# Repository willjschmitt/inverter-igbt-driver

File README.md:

# inverter-igbt-driver
IGBT driver for Electric Vehicle Inverter

This project is a work in progress to design a simple IGBT driver for use with the controls designed in https://github.com/willjschmitt/electric-vehicle-controller.

Board is designed in [KiCad](http://kicad-pcb.org/).

## Getting Started
```
git clone https://github.com/willjschmitt/inverter-igbt-driver
```

Install KiCad. Open up the KiCad project!

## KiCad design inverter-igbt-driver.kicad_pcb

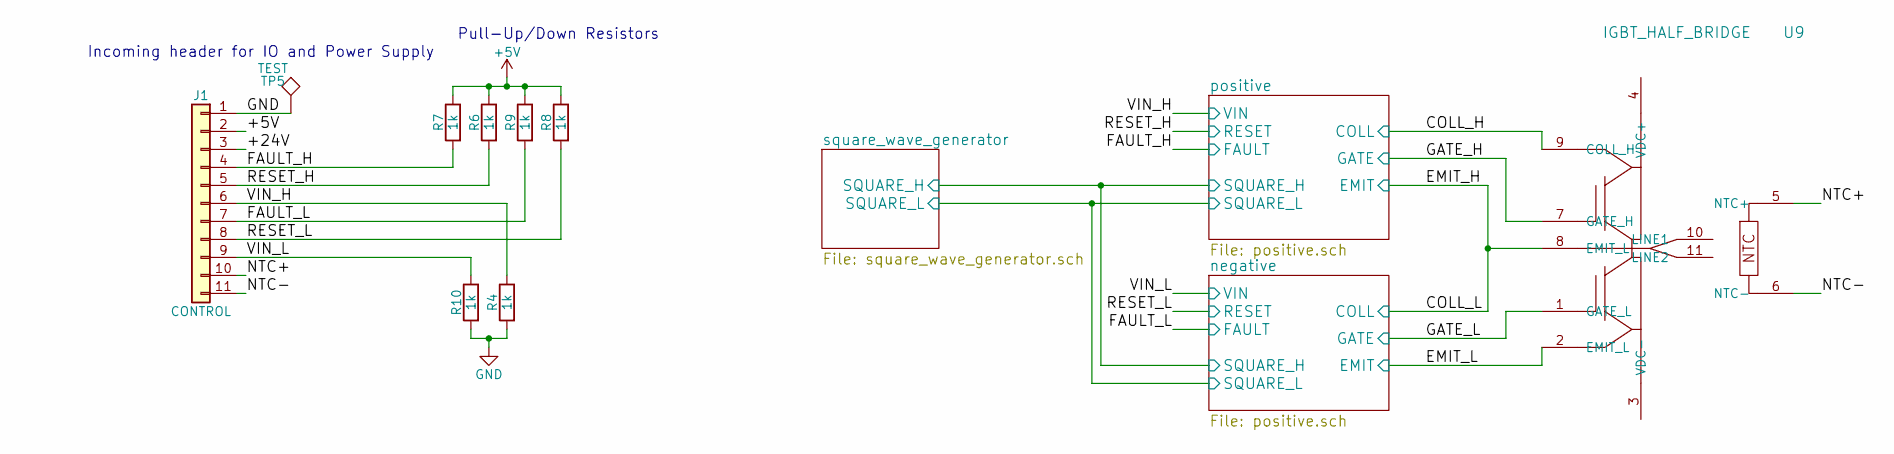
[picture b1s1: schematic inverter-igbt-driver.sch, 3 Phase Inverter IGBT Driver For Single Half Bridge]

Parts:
J1: CONTROL; Pin_Header_Straight_1x11_Pitch2.54mm
R4, R6, R7, R8, R9, R10: 1k; R_0402
TP5: TEST; TP RCT (0805)
U9: IGBT_HALF_BRIDGE; MG06600WB-BN4MM

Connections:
+5V: J1.2, R6.1, R7.1, R8.1, R9.1; also elsewhere on the board
+24V: J1.3; also elsewhere on the board
/COLL_H: U9.9 (COLL_H); also elsewhere on the board
/COLL_L: U9.8 (EMIT_L); also elsewhere on the board
/EMIT_L: U9.2 (EMIT_L); also elsewhere on the board
/FAULT_H: J1.4, R7.2; also elsewhere on the board
/FAULT_L: J1.7, R9.2; also elsewhere on the board
/GATE_H: U9.7 (GATE_H); also elsewhere on the board
/GATE_L: U9.1 (GATE_L); also elsewhere on the board
/NTC+: J1.10, U9.5 (NTC+)
/NTC-: J1.11, U9.6 (NTC-)
/RESET_H: J1.5, R6.2; also elsewhere on the board
/RESET_L: J1.8, R8.2; also elsewhere on the board
/VIN_H: J1.6, R4.1; also elsewhere on the board
/VIN_L: J1.9, R10.1; also elsewhere on the board
GND: J1.1, R4.2, R10.2, TP5.1; also elsewhere on the board

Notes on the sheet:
Incoming header for IO and Power Supply
Pull-Up/Down Resistors

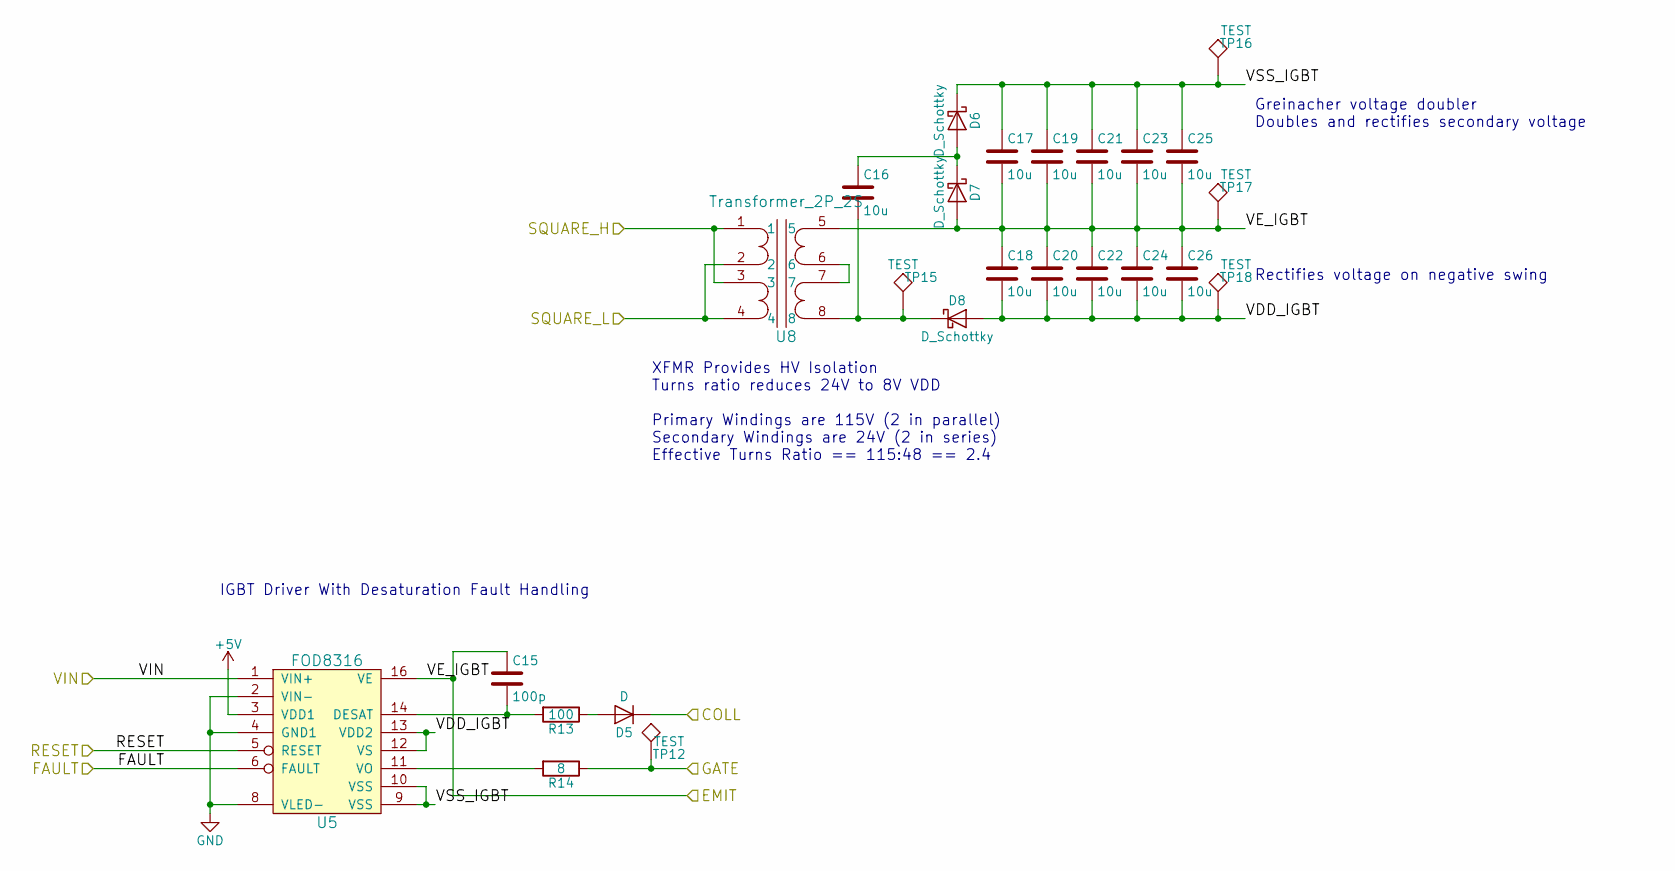
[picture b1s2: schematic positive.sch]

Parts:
C2, C3, C4, C5, C6, C7, C8, C9, C10, C11, C12: 10u; C_1206_HandSoldering
C13: 100p; C_1206_HandSoldering
D1, D2, D3: D_Schottky; D_SOD-123F
D4: D; DO-214AC
R2: 100; R_1206_HandSoldering
R3: 8; R_Axial_DIN0207_L6.3mm_D2.5mm_P7.62mm_Horizontal
TP4, TP6, TP7, TP8, TP9: TEST; TP RCT (0805)
U3: FOD8316; SOIC-16W_7.5x10.3mm_Pitch1.27mm
U6: Transformer_2P_2S; FS48-050-C2

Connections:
+5V: U3.3 (VDD1); also elsewhere on the board
/COLL_H: D4.1 (K); also elsewhere on the board
/COLL_L: C3.2, C4.1, C5.2, C6.1, C7.2, C8.1, C9.2, C10.1, C11.2, C12.1, C13.1, D2.2 (A), TP8.1, U3.16 (VE), U6.5; also elsewhere on the board
/FAULT_H: U3.6 (FAULT); also elsewhere on the board
/GATE_H: R3.1, TP4.1; also elsewhere on the board
/RESET_H: U3.5 (RESET); also elsewhere on the board
/VIN_H: U3.1 (VIN+); also elsewhere on the board
/negative/SQUARE_H: U6.1, U6.3; also elsewhere on the board
/negative/SQUARE_L: U6.2, U6.4; also elsewhere on the board
/positive/VDD_IGBT: C4.2, C6.2, C8.2, C10.2, C12.2, D3.2 (A), TP9.1, U3.12 (VS), U3.13 (VDD2)
/positive/VSS_IGBT: C3.1, C5.1, C7.1, C9.1, C11.1, D1.1 (K), TP7.1, U3.9 (VSS), U3.10 (VSS)
GND: U3.2 (VIN-), U3.4 (GND1), U3.8 (VLED-); also elsewhere on the board
unnamed: C2.1, D1.2 (A), D2.1 (K)
unnamed: C2.2, D3.1 (K), TP6.1, U6.8
unnamed: C13.2, R2.2, U3.14 (DESAT)
unnamed: D4.2 (A), R2.1
unnamed: R3.2, U3.11 (VO)
unnamed: U6.6, U6.7

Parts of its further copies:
C15: 100p; C_1206_HandSoldering
C16, C17, C18, C19, C20, C21, C22, C23, C24, C25, C26: 10u; C_1206_HandSoldering
D5: D; DO-214AC
D6, D7, D8: D_Schottky; D_SOD-123F
R13: 100; R_1206_HandSoldering
R14: 8; R_Axial_DIN0207_L6.3mm_D2.5mm_P7.62mm_Horizontal
TP12, TP15, TP16, TP17, TP18: TEST; TP RCT (0805)
U5: FOD8316; SOIC-16W_7.5x10.3mm_Pitch1.27mm
U8: Transformer_2P_2S; FS48-050-C2

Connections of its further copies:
+5V: U5.3 (VDD1); also elsewhere on the board
/COLL_L: D5.1 (K); also elsewhere on the board
/EMIT_L: C15.1, C17.2, C18.1, C19.2, C20.1, C21.2, C22.1, C23.2, C24.1, C25.2, C26.1, D7.2 (A), TP17.1, U5.16 (VE), U8.5; also elsewhere on the board
/FAULT_L: U5.6 (FAULT); also elsewhere on the board
/GATE_L: R14.1, TP12.1; also elsewhere on the board
/RESET_L: U5.5 (RESET); also elsewhere on the board
/VIN_L: U5.1 (VIN+); also elsewhere on the board
/negative/SQUARE_H: U8.1, U8.3; also elsewhere on the board
/negative/SQUARE_L: U8.2, U8.4; also elsewhere on the board
/negative/VDD_IGBT: C18.2, C20.2, C22.2, C24.2, C26.2, D8.2 (A), TP18.1, U5.12 (VS), U5.13 (VDD2)
/negative/VSS_IGBT: C17.1, C19.1, C21.1, C23.1, C25.1, D6.1 (K), TP16.1, U5.9 (VSS), U5.10 (VSS)
GND: U5.2 (VIN-), U5.4 (GND1), U5.8 (VLED-); also elsewhere on the board
unnamed: C15.2, R13.2, U5.14 (DESAT)
unnamed: C16.1, D6.2 (A), D7.1 (K)
unnamed: C16.2, D8.1 (K), TP15.1, U8.8
unnamed: D5.2 (A), R13.1
unnamed: R14.2, U5.11 (VO)
unnamed: U8.6, U8.7

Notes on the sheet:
XFMR Provides HV Isolation Turns ratio reduces 24V to 8V VDD Primary Windings are 115V (2 in parallel) Secondary Windings are 24V (2 in series) Effective Turns Ratio == 115:48 == 2.4
Greinacher voltage doubler Doubles and rectifies secondary voltage
Rectifies voltage on negative swing
IGBT Driver With Desaturation Fault Handling

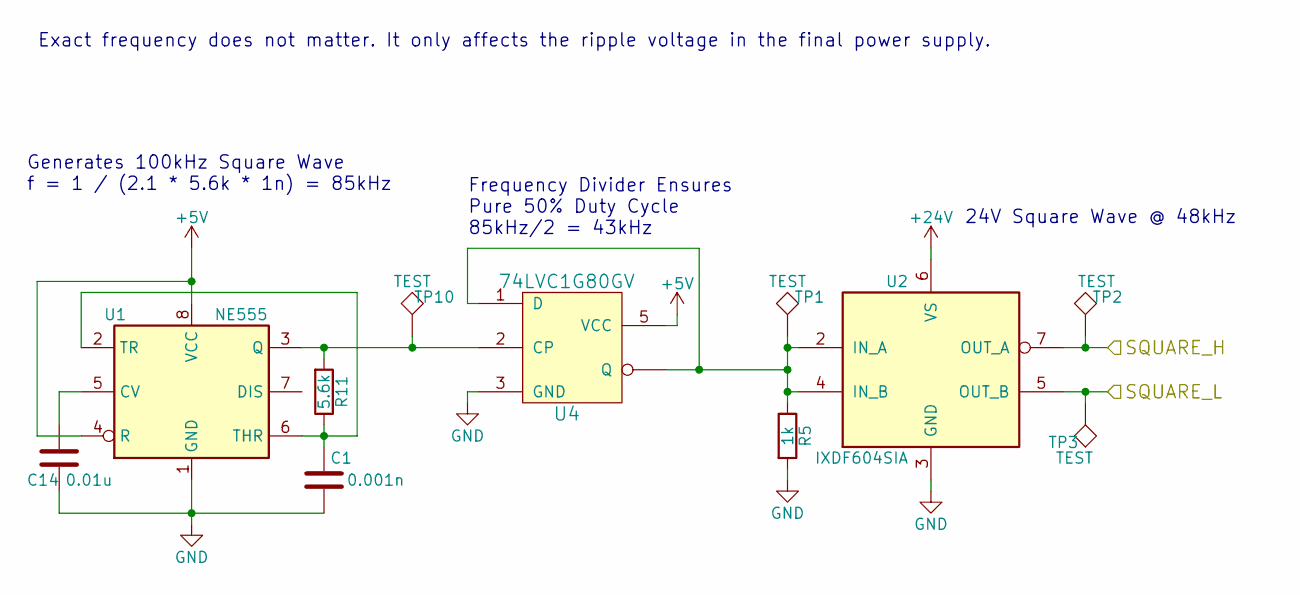
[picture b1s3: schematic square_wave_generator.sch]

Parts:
C1: 0.001n; C_0603_HandSoldering
C14: 0.01u; C_0603_HandSoldering
R5: 1k; R_0402
R11: 5.6k; R_0603_HandSoldering
TP1, TP2, TP3, TP10: TEST; TP RCT (0805)
U1: NE555; SOIC-8_3.9x4.9mm_Pitch1.27mm
U2: IXDF604SIA; SOIC-8_3.9x4.9mm_Pitch1.27mm
U4: 74LVC1G80GV; SOT-353_SC-70-5_Handsoldering

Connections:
+5V: U1.4 (R), U1.8 (VCC), U4.5 (VCC); also elsewhere on the board
+24V: U2.6 (VS); also elsewhere on the board
/negative/SQUARE_H: TP2.1, U2.7 (OUT_A); also elsewhere on the board
/negative/SQUARE_L: TP3.1, U2.5 (OUT_B); also elsewhere on the board
GND: C1.2, C14.2, R5.2, U1.1 (GND), U2.3 (GND), U4.3 (GND); also elsewhere on the board
unnamed: C1.1, R11.1, U1.2 (TR), U1.6 (THR)
unnamed: C14.1, U1.5 (CV)
unnamed: R5.1, TP1.1, U2.2 (IN_A), U2.4 (IN_B), U4.1 (D), U4.~ (Q)
unnamed: R11.2, TP10.1, U1.3 (Q), U4.2 (CP)

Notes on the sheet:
Generates 100kHz Square Wave f = 1 / (2.1 * 5.6k * 1n) = 85kHz
24V Square Wave @ 48kHz
Frequency Divider Ensures Pure 50% Duty Cycle 85kHz/2 = 43kHz
Exact frequency does not matter. It only affects the ripple voltage in the final power supply.

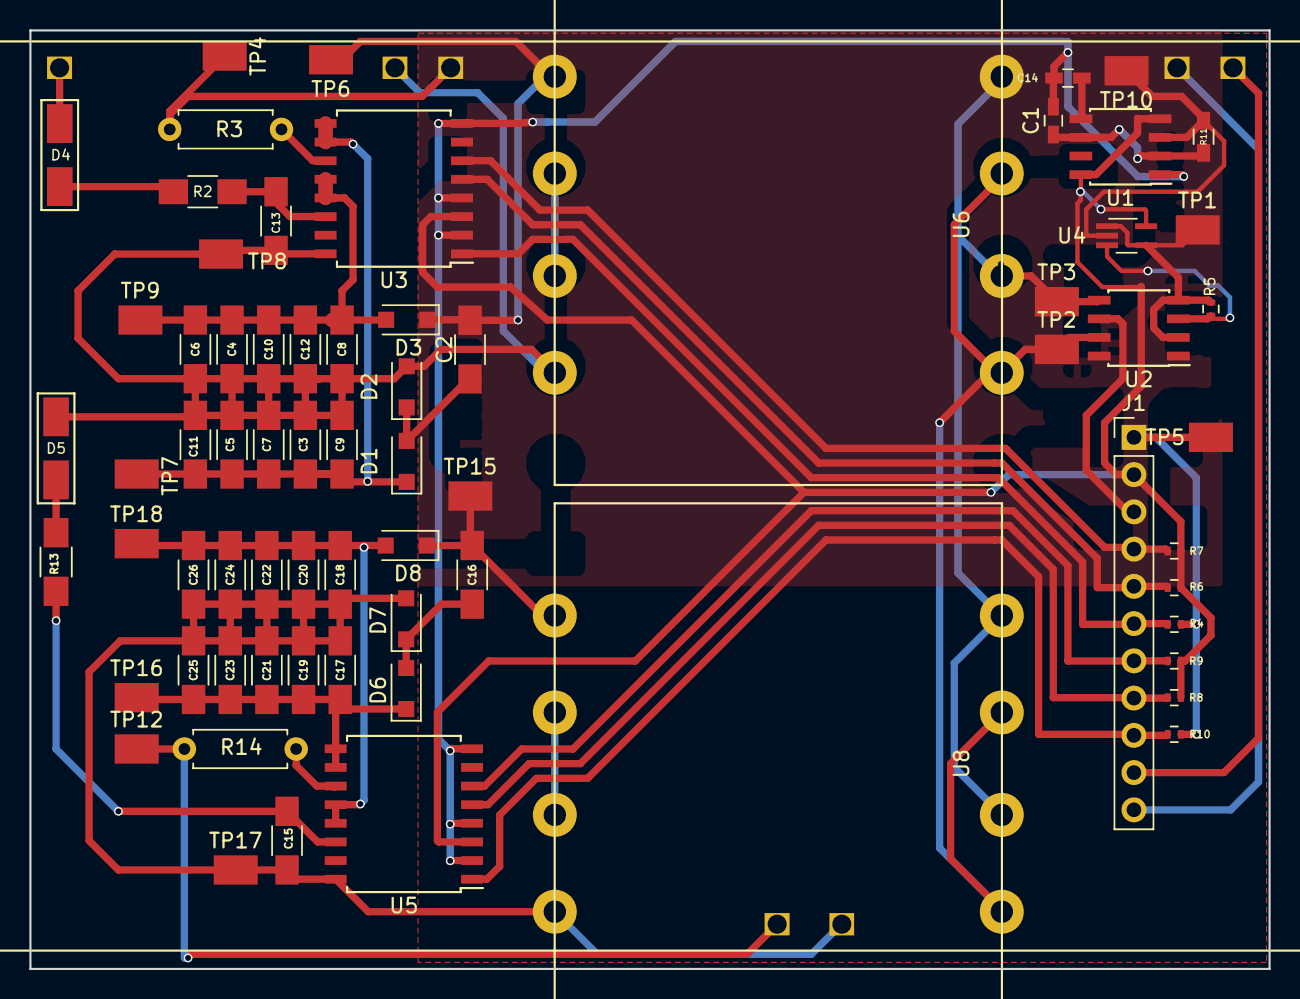
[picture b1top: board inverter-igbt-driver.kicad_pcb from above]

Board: 2 copper layers, 84.5 x 64.0 mm, 70 parts (0 on the bottom side), 38 nets.

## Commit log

2018-04-10 First attempt at a complete IGBT driver.
2018-04-10 Adds pull-down resistors for logic nets.
2018-04-10 Add GND test point.
2018-04-10 Fix emitter connection.
2018-04-11 Switching pull-down to pull-up resistors for fault/reset.
2018-04-11 Add lib file.
2018-04-20 Refactor into schematic.
2018-04-20 Fix test point connection.
2018-04-21 Including both igbt drivers on one board.
    WIP
2018-04-21 Add _H suffix to hot leg.
2018-04-21 Move square wave generator to single module.
2018-04-21 Fixing layout
2018-04-22 Completed layout with one connector.
2018-04-29 Wire adjustments
2018-05-05 Changed 555 timer configuration.
    555 timer was not behaving correctly. Added resistor to out for timing and increased resistor to 5V to mostly open circuit (in steady state).
    Added extra coupling capacitor for control voltage.
2018-05-05 Adds NTC to connector.
    Completes 555 rewire.
    Rewires IGBT signals to layout more simply.
2018-05-05 Fix hole size for avoiding slotting in OshPark drilling.
2018-05-05 Cleaning up layout of main connector.
2018-05-05 Ignore cache lib file.
2018-05-06 Adds library cache.
2018-05-08 Changing 555 timer again to remove pullup resistor and discharge.
2018-05-08 Adding d-flop to achieve 50% duty cycle
    555 timer config cannot guarantee 50% duty cycle, but a frequency divider can.
2018-05-11 Adjust resistor value and cap values for pulse generator
2018-05-11 Update values.
